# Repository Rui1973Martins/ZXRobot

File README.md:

# ZXRobot
Implementation of all required software and hardware layers to control a Semi Professional Robot Arm, using a ZX Spectrum 48K.

## Included projects

- SerialRS232Dual
  Hardware PCB and and firmware driver in Z80 Assembly

  Requires Pasmo Assembler to compile (compile.bat)

- TicTacToe
  Implemetaion of Tic-Tac-Toe game (to be integrated with Robot arm movement commands, in future)
  
  Requries Make and Pasmo assembler to compile (make all)

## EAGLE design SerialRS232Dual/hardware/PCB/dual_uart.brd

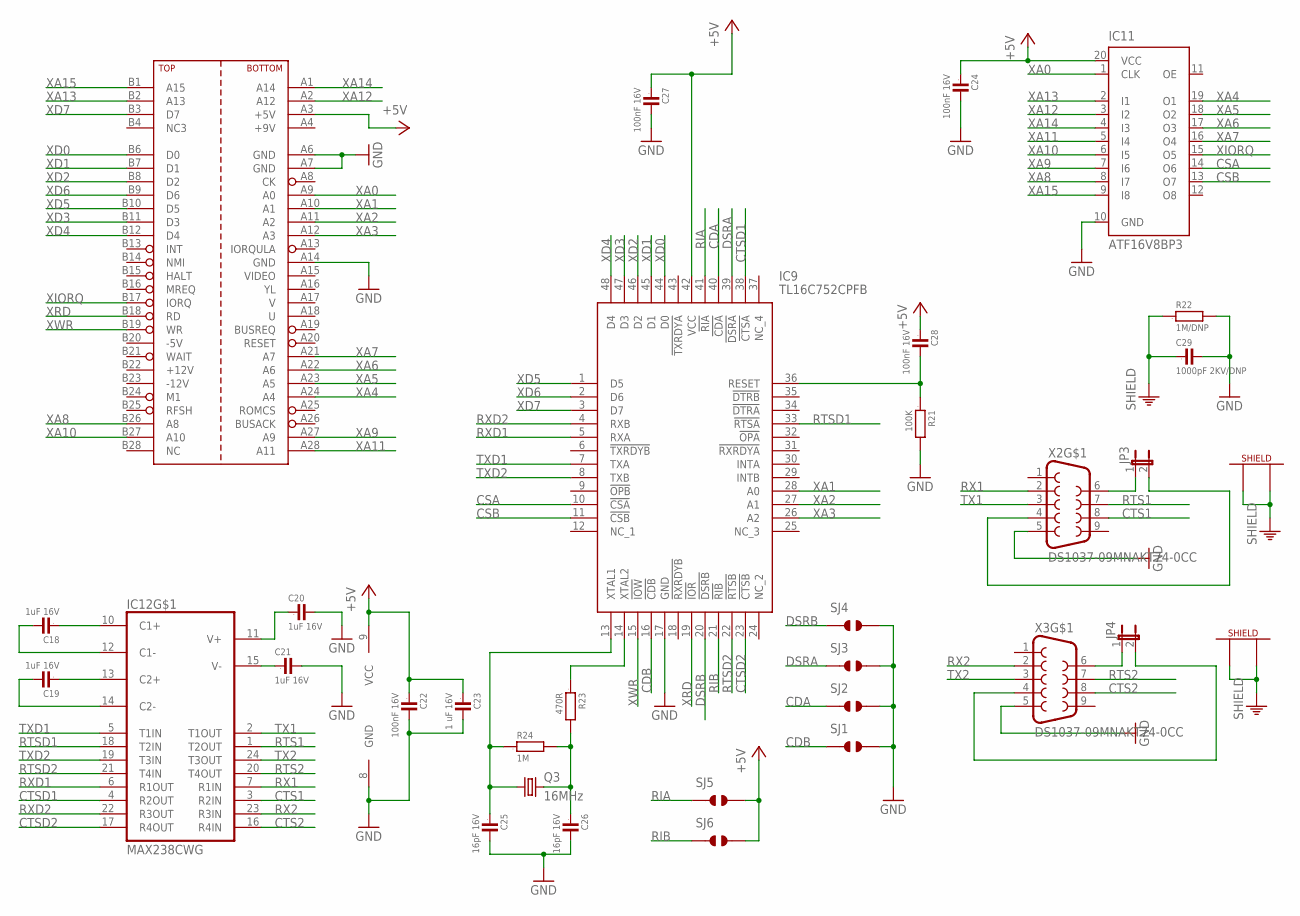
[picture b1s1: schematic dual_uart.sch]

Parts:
C18, C19, C20, C21: 1uF 16V; 0603
C22, C24, C27, C28: 100nF 16V; 0603
C23: 1 uF 16V; 0603
C25, C26: 16pF 16V; 0603
C29: 1000pF 2KV/DNP; 1210
CONN2: ZX_EDGE_DAUGHTERBOARD; ZX-EDGE-DAUGHTERBOARD@1
IC9: TL16C752CPFB; QFP50P900X900X120-48N
IC11: ATF16V8BP3; DIL20
IC12: MAX238CWG; SO24L
JP3, JP4: JP1E; JP1
Q3: 16MHz; HC49/S
R21: 100K; 0603
R22: 1M/DNP; 0805
R23: 470R; 0603
R24: 1M; 0603
SJ1, SJ2, SJ3, SJ4, SJ5, SJ6: JUMPER_SOLDER_1X2
X2, X3: DS1037-09MNAKT74-0CC; DB9_MALE

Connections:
+5V: C22.1, C23.1, C24.1, C27.1, C28.1, CONN2.A3 (+5V), IC9.42 (VCC), IC11.20 (VCC), IC12.9 (VCC), SJ5.2, SJ6.2
+9V: CONN2.A4 (+9V)
+12V: CONN2.B22 (+12V)
-5V: CONN2.B20 (-5V)
-12V: CONN2.B23 (-12V)
CDA: IC9.40 (!CDA), SJ2.1
CDB: IC9.16 (!CDB), SJ1.1
CSA: IC9.10 (!CSA), IC11.14 (O6)
CSB: IC9.11 (!CSB), IC11.13 (O7)
CTS1: IC12.3 (R2IN), X2.8
CTS2: IC12.16 (R4IN), X3.8
CTSD1: IC9.38 (!CTSA), IC12.4 (R2OUT)
CTSD2: IC9.23 (!CTSB), IC12.17 (R4OUT)
DSRA: IC9.39 (!DSRA), SJ3.1
DSRB: IC9.20 (!DSRB), SJ4.1
GND: C20.2, C21.2, C22.2, C23.2, C24.2, C25.2, C26.2, C27.2, C29.2, CONN2.A6 (GND), CONN2.A7 (GND), CONN2.A14 (GND), IC9.17 (GND), IC11.10 (GND), IC12.8 (GND), R21.2, R22.2, SJ1.2, SJ2.2, SJ3.2, SJ4.2, X2.5, X3.5
unnamed: C21.1, IC12.15 (V-)
unnamed: C20.1, IC12.11 (V+)
unnamed: C18.2, IC12.12 (C1-)
unnamed: C18.1, IC12.10 (C1+)
unnamed: C19.1, IC12.13 (C2+)
unnamed: C19.2, IC12.14 (C2-)
unnamed: JP4.1, X3.6
unnamed: JP4.2, X3.4
unnamed: JP3.1, X2.6
unnamed: JP3.2, X2.4
unnamed: C26.1, Q3.2, R23.2, R24.2
unnamed: C25.1, IC9.13 (XTAL1), Q3.1, R24.1
unnamed: IC9.14 (XTAL2), R23.1
unnamed: C28.2, IC9.36 (RESET), R21.1
PE: C29.1, R22.1, X2.G1, X2.G2, X3.G1, X3.G2
RIA: IC9.41 (!RIA), SJ5.1
RIB: IC9.21 (!RIB), SJ6.1
RTS1: IC12.1 (T2OUT), X2.7
RTS2: IC12.20 (T4OUT), X3.7
RTSD1: IC9.33 (!RTSA), IC12.18 (T2IN)
RTSD2: IC9.22 (!RTSB), IC12.21 (T4IN)
RX1: IC12.7 (R1IN), X2.2
RX2: IC12.23 (R3IN), X3.2
RXD1: IC9.5 (RXA), IC12.6 (R1OUT)
RXD2: IC9.4 (RXB), IC12.22 (R3OUT)
TX1: IC12.2 (T1OUT), X2.3
TX2: IC12.24 (T3OUT), X3.3
TXD1: IC9.7 (TXA), IC12.5 (T1IN)
TXD2: IC9.8 (TXB), IC12.19 (T3IN)
XA0: CONN2.A9 (A0), IC11.1 (CLK)
XA1: CONN2.A10 (A1), IC9.28 (A0)
XA2: CONN2.A11 (A2), IC9.27 (A1)
XA3: CONN2.A12 (A3), IC9.26 (A2)
XA4: CONN2.A24 (A4), IC11.19 (O1)
XA5: CONN2.A23 (A5), IC11.18 (O2)
XA6: CONN2.A22 (A6), IC11.17 (O3)
XA7: CONN2.A21 (A7), IC11.16 (O4)
XA8: CONN2.B26 (A8), IC11.8 (I7)
XA9: CONN2.A27 (A9), IC11.7 (I6)
XA10: CONN2.B27 (A10), IC11.6 (I5)
XA11: CONN2.A28 (A11), IC11.5 (I4)
XA12: CONN2.A2 (A12), IC11.3 (I2)
XA13: CONN2.B2 (A13), IC11.2 (I1)
XA14: CONN2.A1 (A14), IC11.4 (I3)
XA15: CONN2.B1 (A15), IC11.9 (I8)
XD0: CONN2.B6 (D0), IC9.44 (D0)
XD1: CONN2.B7 (D1), IC9.45 (D1)
XD2: CONN2.B8 (D2), IC9.46 (D2)
XD3: CONN2.B11 (D3), IC9.47 (D3)
XD4: CONN2.B12 (D4), IC9.48 (D4)
XD5: CONN2.B10 (D5), IC9.1 (D5)
XD6: CONN2.B9 (D6), IC9.2 (D6)
XD7: CONN2.B3 (D7), IC9.3 (D7)
XIORQ: CONN2.B17 (IORQ), IC11.15 (O5)
XRD: CONN2.B18 (RD), IC9.19 (!IOR)
XWR: CONN2.B19 (WR), IC9.15 (!IOW)

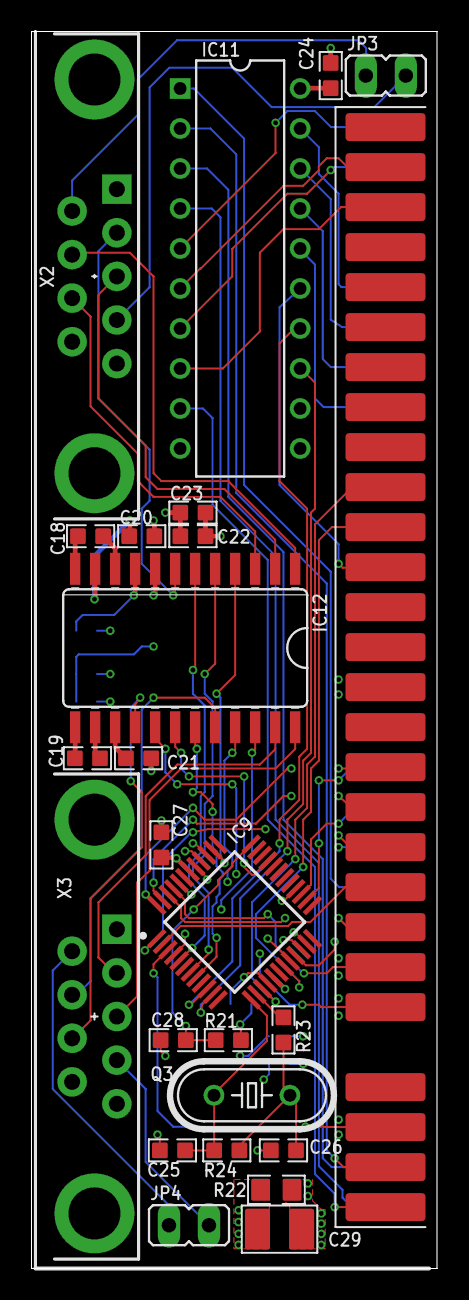
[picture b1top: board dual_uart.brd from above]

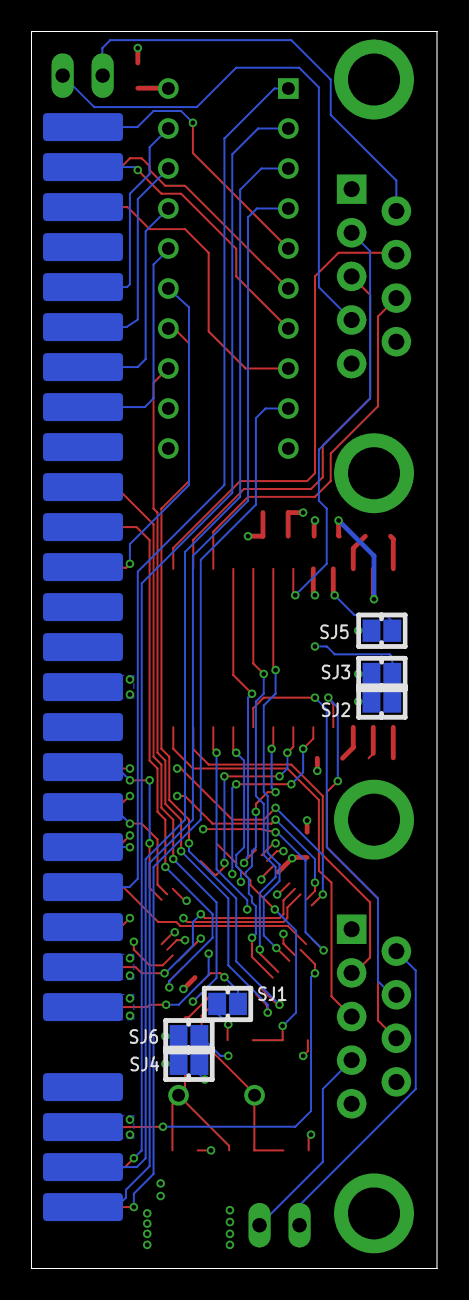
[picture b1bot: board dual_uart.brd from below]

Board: 4 copper layers, 25.8 x 78.5 mm, 31 parts (6 on the bottom side), 68 nets.

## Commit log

2024-02-02 Hardware PCB
2024-02-02 Firmware
2024-02-02 Add TicTacToe game.

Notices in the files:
parts and their libraries:
SparkFun-Connectors: Licensing: CC v3.0 Share-Alike You are welcome to use this library for commercial purposes.
